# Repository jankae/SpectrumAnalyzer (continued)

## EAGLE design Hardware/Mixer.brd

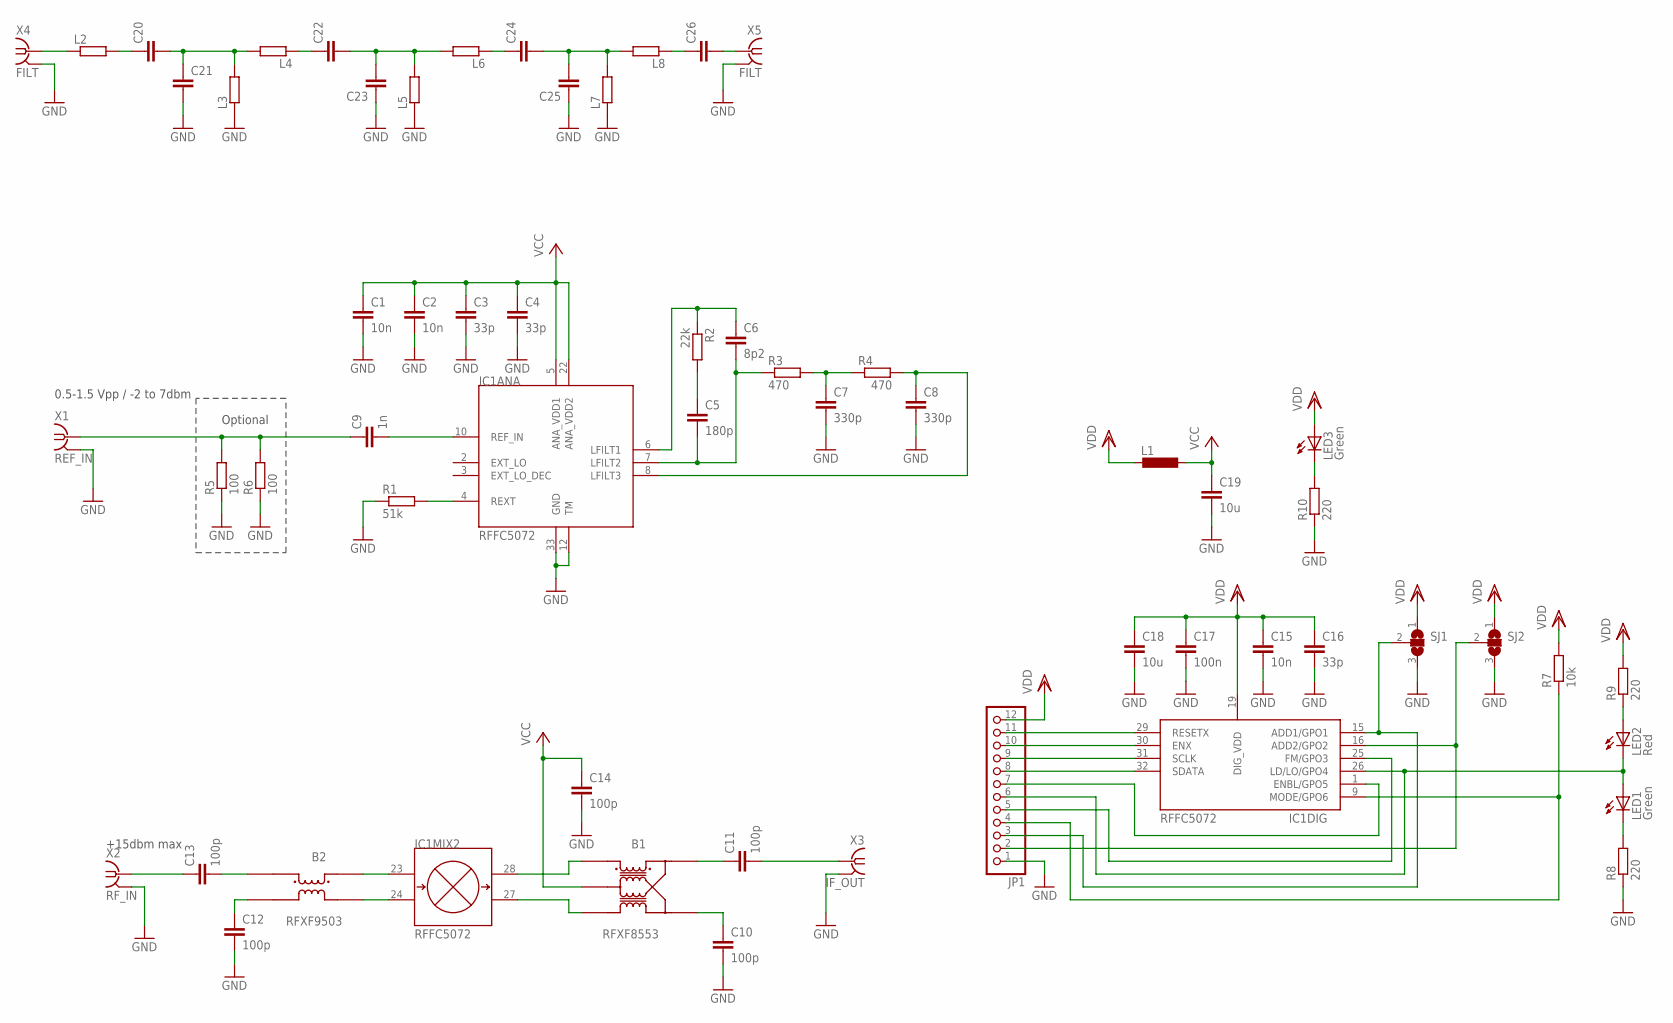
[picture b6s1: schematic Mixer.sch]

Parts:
B1: RFXF8553; S20
B2: RFXF9503; S20
C1, C2, C15: 10n; C0603
C3, C4, C16: 33p; C0603
C5: 180p; C0603
C6: 8p2; C0603
C7, C8: 330p; C0603
C9: 1n; C0603
C10, C11, C12, C13, C14: 100p; C0603
C17: 100n; C0603
C18, C19: 10u; C1206
C20, C21, C22, C23, C24, C25, C26: C-EUC0603; C0603
IC1: RFFC5072; QFN50P500X500X95-33T370
JP1: PINHD-1X12/90; 1X12/90
L1: L-EUL2012C; L2012C
L2, L3, L4, L5, L6, L7, L8: R-EU_R0603; R0603
LED1, LED3: Green; LED_SML0603
LED2: Red; LED_SML0603
R1: 51k; R0603
R2: 22k; R0603
R3, R4: 470; R0603
R5, R6: 100; R0603
R7: 10k; R0603
R8, R9, R10: 220; R0603
SJ1, SJ2: SJ2W; SJ_2
X1: REF_IN; J502-ND-142-0701-881/886
X2: RF_IN; J502-ND-142-0701-881/886
X3: IF_OUT; J502-ND-142-0701-881/886
X4, X5: FILT; J502-ND-142-0701-881/886

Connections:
GND: C1.2, C2.2, C3.2, C4.2, C7.2, C8.2, C10.2, C12.2, C14.2, C15.2, C16.2, C17.2, C18.2, C19.2, C21.2, C23.1, C25.1, IC1.12 (TM), IC1.33 (GND), JP1.1, L3.1, L5.1, L7.1, R1.1, R5.1, R6.1, R8.1, R10.1, SJ1.3, SJ2.3, X1.G@1 (2), X1.G@2 (2), X1.G@3 (2), X1.G@4 (2), X2.G@1 (2), X2.G@2 (2), X2.G@3 (2), X2.G@4 (2), X3.G@1 (2), X3.G@2 (2), X3.G@3 (2), X3.G@4 (2), X4.G@1 (2), X4.G@2 (2), X4.G@3 (2), X4.G@4 (2), X5.G@1 (2), X5.G@2 (2), X5.G@3 (2), X5.G@4 (2)
unnamed: IC1.4 (REXT), R1.2
unnamed: IC1.9 (MODE/GPO6), JP1.4, R7.1
unnamed: C6.1, IC1.6 (LFILT1), R2.1
unnamed: C5.2, C6.2, IC1.7 (LFILT2), R3.1
unnamed: C5.1, R2.2
unnamed: C7.1, R3.2, R4.1
unnamed: C8.1, IC1.8 (LFILT3), R4.2
unnamed: C9.2, IC1.10 (REF_IN)
unnamed: C9.1, R5.2, R6.2, X1.1
unnamed: B2.P$3 (3), IC1.23 (IPP)
unnamed: B2.P$1 (1), IC1.24 (IPN)
unnamed: B1.P$1 (1), IC1.28 (OPP)
unnamed: B1.P$3 (3), IC1.27 (OPN)
unnamed: LED1.C, R8.2
unnamed: B2.P$5 (5), C12.1
unnamed: B2.P$4 (4), C13.2
unnamed: B1.P$5 (5), C10.1
unnamed: B1.P$4 (4), C11.1
unnamed: C13.1, X2.1
unnamed: C11.2, X3.1
unnamed: IC1.15 (ADD1/GPO1), JP1.3, SJ1.2
unnamed: LED2.A, R9.1
unnamed: IC1.26 (LD/LO/GPO4), JP1.6, LED1.A, LED2.C
unnamed: IC1.16 (ADD2/GPO2), JP1.2, SJ2.2
unnamed: IC1.29 (RESETX), JP1.11
unnamed: IC1.30 (ENX), JP1.10
unnamed: IC1.31 (SCLK), JP1.9
unnamed: IC1.32 (SDATA), JP1.8
unnamed: LED3.C, R10.2
unnamed: IC1.1 (ENBL/GPO5), JP1.7
unnamed: L2.1, X4.1
unnamed: IC1.25 (FM/GPO3), JP1.5
unnamed: C20.1, L2.2
unnamed: C20.2, C21.1, L3.2, L4.2
unnamed: C22.1, L4.1
unnamed: C22.2, C23.2, L5.2, L6.2
unnamed: C24.1, L6.1
unnamed: C24.2, C25.2, L7.2, L8.2
unnamed: C26.1, L8.1
unnamed: C26.2, X5.1
VCC: B1.P$2 (2), C1.1, C2.1, C3.1, C4.1, C14.1, C19.1, IC1.5 (ANA_VDD1), IC1.22 (ANA_VDD2), L1.1
VDD: C15.1, C16.1, C17.1, C18.1, IC1.19 (DIG_VDD), JP1.12, L1.2, LED3.A, R7.2, R9.2, SJ1.1, SJ2.1

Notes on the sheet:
Optional
0.5-1.5 Vpp / -2 to 7dbm
+15dbm max

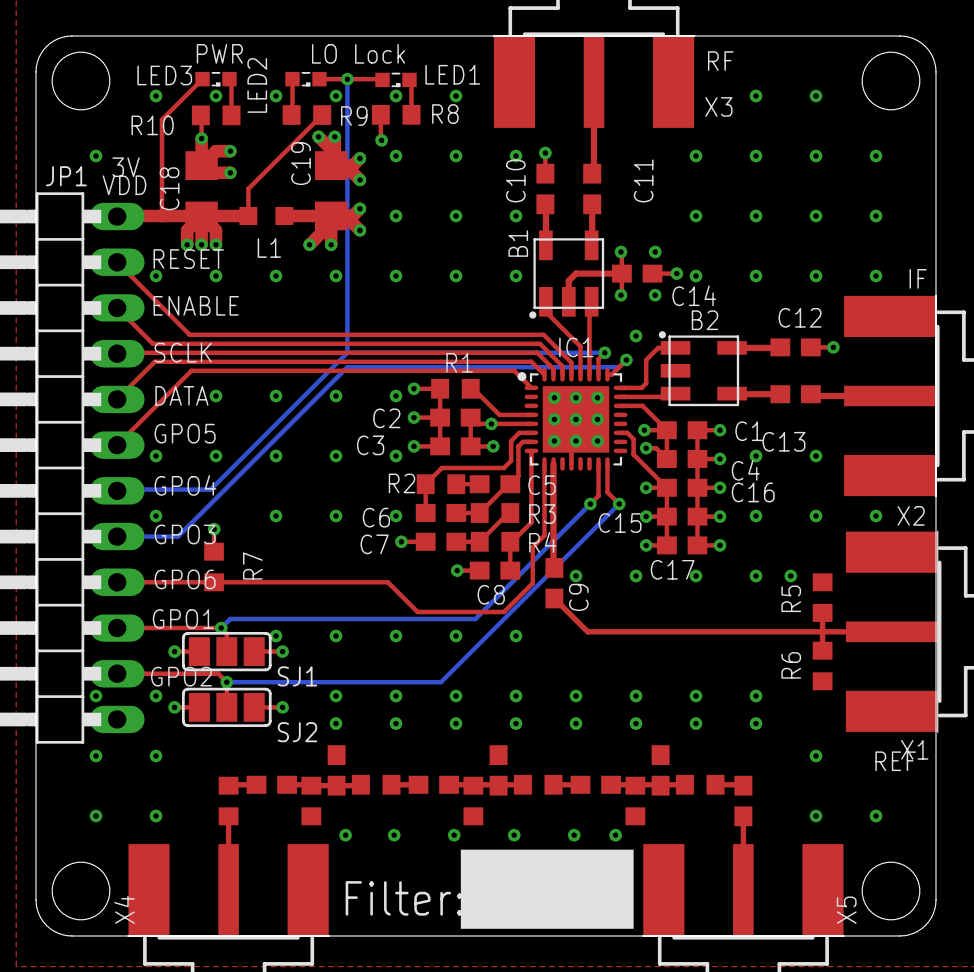
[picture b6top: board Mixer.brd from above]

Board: 4 copper layers, 50.0 x 50.0 mm, 58 parts (0 on the bottom side), 43 nets.

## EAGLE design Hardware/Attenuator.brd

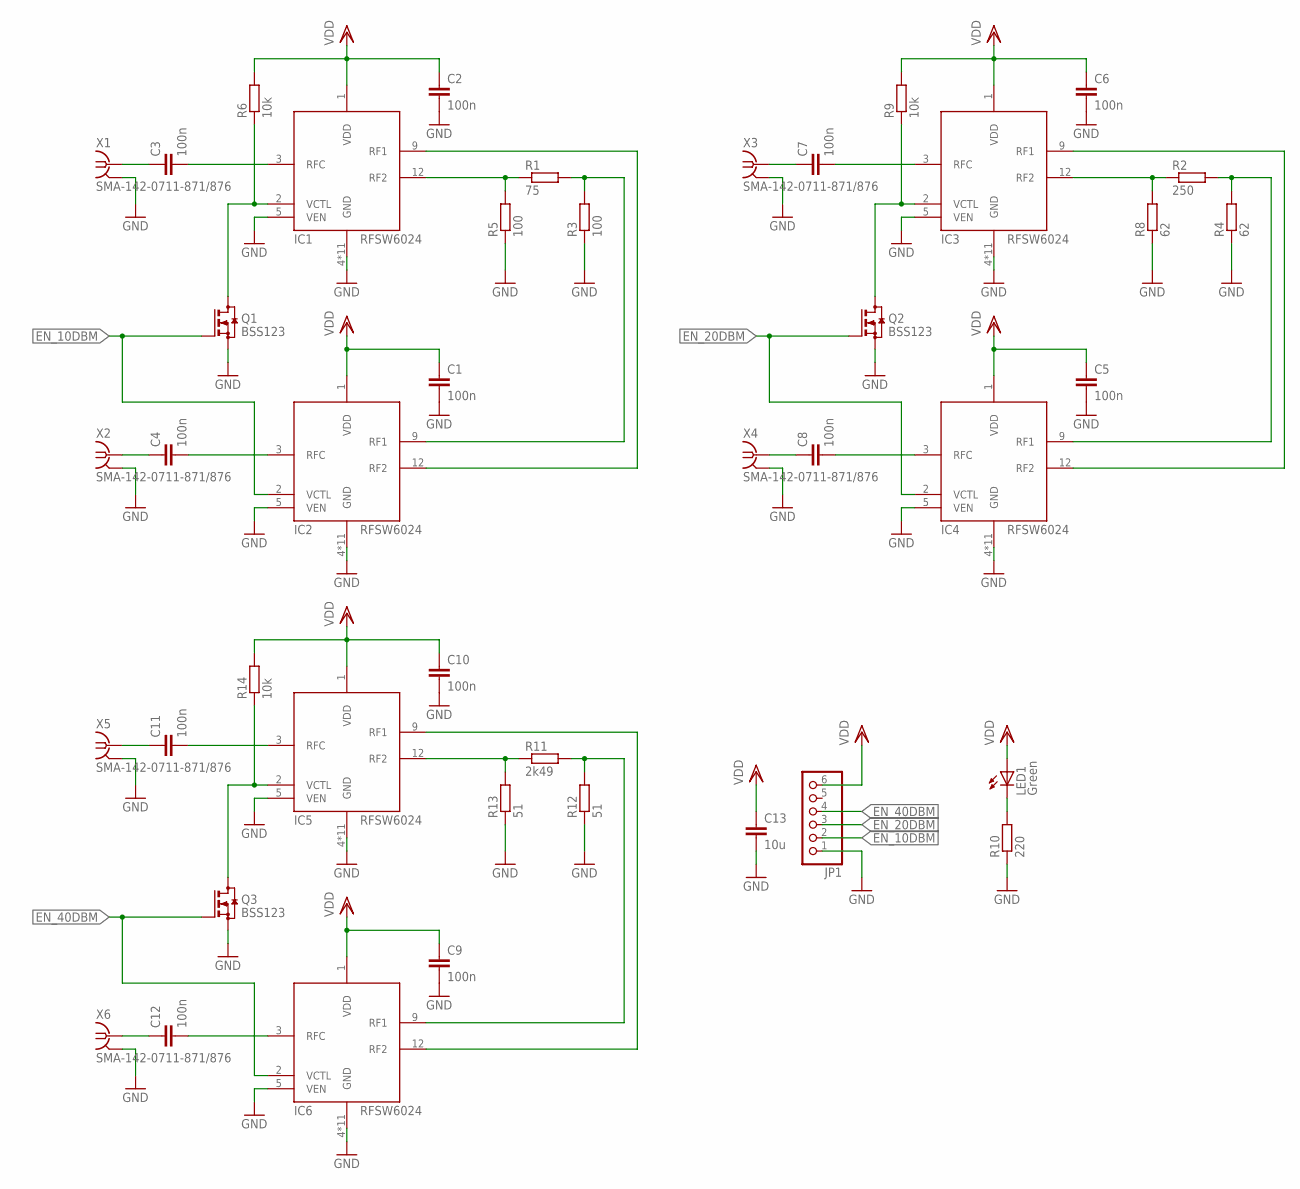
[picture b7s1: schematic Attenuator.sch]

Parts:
C1, C2, C3, C4, C5, C6, C7, C8, C9, C10, C11, C12: 100n; C0603K
C13: 10u; C1206
IC1, IC2, IC3, IC4, IC5, IC6: RFSW6024; QFN16
JP1: PINHD-1X6/90; 1X06/90
LED1: Green; LED_SML0603
Q1, Q2, Q3: BSS123; SOT23
R1: 75; R0603
R2: 250; R0603
R3, R5: 100; R0603
R4, R8: 62; R0603
R6, R9, R14: 10k; R0603
R10: 220; R0603
R11: 2k49; R0603
R12, R13: 51; R0603
X1, X2, X3, X4, X5, X6: SMA-142-0711-871/876; J502-ND-142-0711-871/876

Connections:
EN_10DBM: IC2.2 (VCTL), JP1.2, Q1.1 (G)
EN_20DBM: IC4.2 (VCTL), JP1.3, Q2.1 (G)
EN_40DBM: IC6.2 (VCTL), JP1.4, Q3.1 (G)
GND: C1.2, C2.2, C5.2, C6.2, C9.2, C10.2, C13.2, IC1.4 (GND), IC1.5 (VEN), IC1.6 (GND), IC1.7 (GND), IC1.8 (GND), IC1.10 (GND), IC1.11 (GND), IC1.13 (GND), IC1.14 (GND), IC1.15 (GND), IC1.16 (GND), IC1.17 (GND), IC2.4 (GND), IC2.5 (VEN), IC2.6 (GND), IC2.7 (GND), IC2.8 (GND), IC2.10 (GND), IC2.11 (GND), IC2.13 (GND), IC2.14 (GND), IC2.15 (GND), IC2.16 (GND), IC2.17 (GND), IC3.4 (GND), IC3.5 (VEN), IC3.6 (GND), IC3.7 (GND), IC3.8 (GND), IC3.10 (GND), IC3.11 (GND), IC3.13 (GND), IC3.14 (GND), IC3.15 (GND), IC3.16 (GND), IC3.17 (GND), IC4.4 (GND), IC4.5 (VEN), IC4.6 (GND), IC4.7 (GND), IC4.8 (GND), IC4.10 (GND), IC4.11 (GND), IC4.13 (GND), IC4.14 (GND), IC4.15 (GND), IC4.16 (GND), IC4.17 (GND), IC5.4 (GND), IC5.5 (VEN), IC5.6 (GND), IC5.7 (GND), IC5.8 (GND), IC5.10 (GND), IC5.11 (GND), IC5.13 (GND), IC5.14 (GND), IC5.15 (GND), IC5.16 (GND), IC5.17 (GND), IC6.4 (GND), IC6.5 (VEN), IC6.6 (GND), IC6.7 (GND), IC6.8 (GND), IC6.10 (GND), IC6.11 (GND), IC6.13 (GND), IC6.14 (GND), IC6.15 (GND), IC6.16 (GND), IC6.17 (GND), JP1.1, Q1.2 (S), Q2.2 (S), Q3.2 (S), R3.1, R4.1, R5.1, R8.1, R10.1, R12.1, R13.1, X1.G@1 (2), X1.G@2 (2), X1.G@3 (2), X1.G@4 (2), X2.G@1 (2), X2.G@2 (2), X2.G@3 (2), X2.G@4 (2), X3.G@1 (2), X3.G@2 (2), X3.G@3 (2), X3.G@4 (2), X4.G@1 (2), X4.G@2 (2), X4.G@3 (2), X4.G@4 (2), X5.G@1 (2), X5.G@2 (2), X5.G@3 (2), X5.G@4 (2), X6.G@1 (2), X6.G@2 (2), X6.G@3 (2), X6.G@4 (2)
unnamed: IC1.9 (RF1), IC2.12 (RF2)
unnamed: IC1.12 (RF2), R1.1, R5.2
unnamed: IC2.9 (RF1), R1.2, R3.2
unnamed: IC3.12 (RF2), R2.1, R8.2
unnamed: C3.2, IC1.3 (RFC)
unnamed: C4.2, IC2.3 (RFC)
unnamed: C4.1, X2.1
unnamed: C3.1, X1.1
unnamed: IC1.2 (VCTL), Q1.3 (D), R6.1
unnamed: IC4.9 (RF1), R2.2, R4.2
unnamed: IC3.9 (RF1), IC4.12 (RF2)
unnamed: C7.2, IC3.3 (RFC)
unnamed: C8.2, IC4.3 (RFC)
unnamed: C8.1, X4.1
unnamed: C7.1, X3.1
unnamed: IC3.2 (VCTL), Q2.3 (D), R9.1
unnamed: IC5.12 (RF2), R11.1, R13.2
unnamed: IC6.9 (RF1), R11.2, R12.2
unnamed: IC5.9 (RF1), IC6.12 (RF2)
unnamed: C11.2, IC5.3 (RFC)
unnamed: C12.2, IC6.3 (RFC)
unnamed: C12.1, X6.1
unnamed: C11.1, X5.1
unnamed: IC5.2 (VCTL), Q3.3 (D), R14.1
unnamed: LED1.C, R10.2
VDD: C1.1, C2.1, C5.1, C6.1, C9.1, C10.1, C13.1, IC1.1 (VDD), IC2.1 (VDD), IC3.1 (VDD), IC4.1 (VDD), IC5.1 (VDD), IC6.1 (VDD), JP1.6, LED1.A, R6.2, R9.2, R14.2

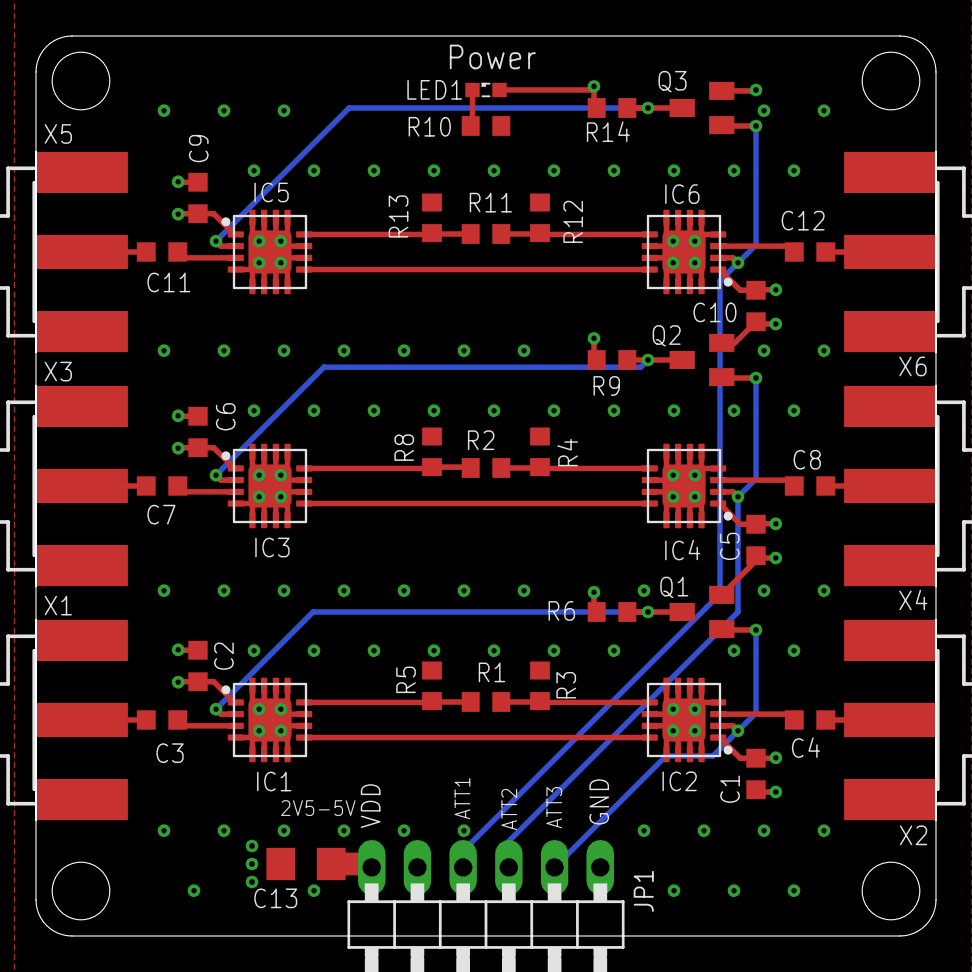
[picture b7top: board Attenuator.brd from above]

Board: 4 copper layers, 50.0 x 50.0 mm, 43 parts (0 on the bottom side), 30 nets.

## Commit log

2019-03-10 PCB layouts, partial ADC+FFT for Spartan6, FPGA SPI test
2019-03-10 Subset of DG1022 functionality implemnted
2019-03-12 FPGA + CPU fft implementation
2019-03-13 FPGA whole FFT simulation + MCU dummy ADC data generation
2019-03-16 SPI slave clocked by SPI_CLK
2019-03-16 SPI slave improved but still some issues
2019-03-16 Experiments with SPI clocked by SCLK
2019-03-16 Bugfixes for single bin FFT
2019-03-17 Speed improvements
2019-03-17 Created flash configuration file
2019-03-22 ADC sample speed test in FPGA
2019-03-23 Further tests with SPI clocked by SPI_CLK
2019-03-23 FFT of real ADC data in MCU
2019-03-24 RFFC5072 driver
2019-04-02 Filter tests + ADC FFT results
2019-04-13 Further experiments/scripts
2019-04-27 Amplifier board
2019-04-27 Data from cavity filter
2019-04-27 Minor changes in mixer settings
2019-04-27 Ability to set reference level
2019-05-01 More experimental PCB designs
2019-05-05 Adjustments for FFT in FPGA test
2019-05-05 New Gerber files
2019-05-06 Fix ADC sampling issues in FPGA
2019-05-23 RF test update
2019-05-24 First complete spectrum analyzer test
2019-06-22 final FPGA changes
2019-06-22 Slight shift of 1.IF to prevent feedthrough
2019-06-22 Pictures and results
2019-06-22 Minor optimization
2019-06-22 .gitignore update
2019-06-22 Pinout of Nucleo for test setup
2019-06-22 Removed old bandpass calculations
